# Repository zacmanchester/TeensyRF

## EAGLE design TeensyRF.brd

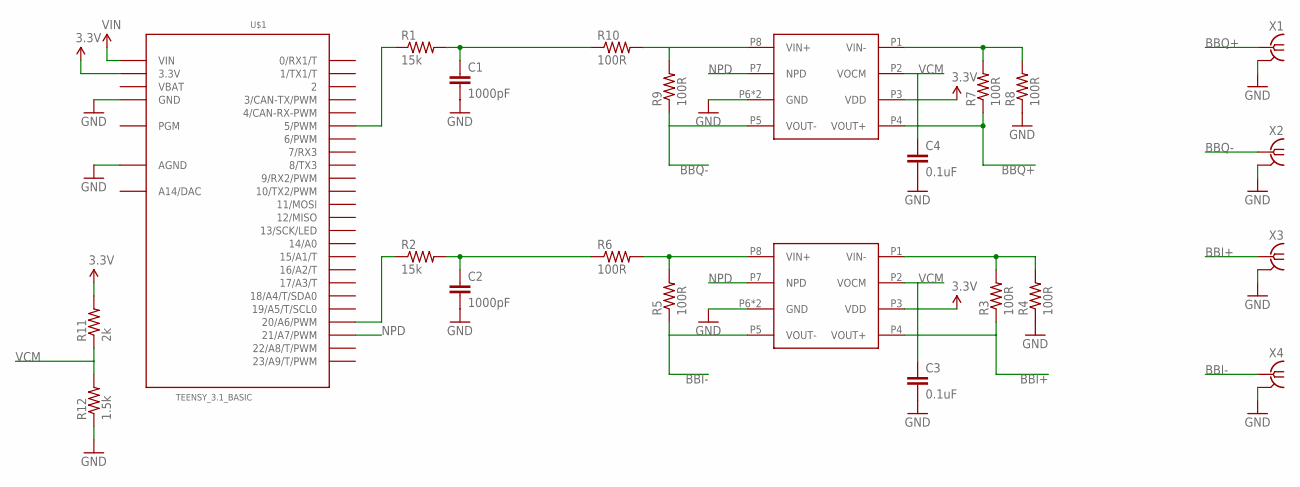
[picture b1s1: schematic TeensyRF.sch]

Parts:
C1, C2: 1000pF; 0805
C3, C4: 0.1uF; 0805
R1, R2: 15k; 0805
R3, R4, R5, R6, R7, R8, R9, R10: 100R; 0805
R11: 2k; 0805
R12: 1.5k; 0805
U$1: TEENSY_3.1_BASIC
U$2, U$3: THS4120; POWERPAD-MSOP-8
X1, X2, X3, X4: SMA-142-0701-801/806; J502-ND-142-0701-801/806

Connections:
3.3V: R11.2, U$1.3.3V, U$1.3.3V1 (3.3V), U$2.P3 (VDD), U$3.P3 (VDD)
BBI+: R3.1, U$3.P4 (VOUT+), X3.1
BBI-: R5.1, U$3.P5 (VOUT-), X4.1
BBQ+: R7.1, U$2.P4 (VOUT+), X1.1
BBQ-: R9.1, U$2.P5 (VOUT-), X2.1
GND: C1.2, C2.2, C3.2, C4.2, R4.1, R8.1, R12.1, U$1.AGND, U$1.GND, U$1.GND1 (GND), U$2.P6 (GND), U$2.PAD (GND), U$3.P6 (GND), U$3.PAD (GND), X1.G@1 (2), X1.G@2 (2), X1.G@3 (2), X1.G@4 (2), X2.G@1 (2), X2.G@2 (2), X2.G@3 (2), X2.G@4 (2), X3.G@1 (2), X3.G@2 (2), X3.G@3 (2), X3.G@4 (2), X4.G@1 (2), X4.G@2 (2), X4.G@3 (2), X4.G@4 (2)
unnamed: R1.1, U$1.5 (5/PWM)
unnamed: C1.1, R1.2, R10.1
unnamed: R2.1, U$1.20/A6 (20/A6/PWM)
unnamed: C2.1, R2.2, R6.1
unnamed: R5.2, R6.2, U$3.P8 (VIN+)
unnamed: R3.2, R4.2, U$3.P1 (VIN-)
unnamed: R7.2, R8.2, U$2.P1 (VIN-)
unnamed: R9.2, R10.2, U$2.P8 (VIN+)
NPD: U$1.21/A7 (21/A7/PWM), U$2.P7 (NPD), U$3.P7 (NPD)
VBAT: U$1.VBAT
VCM: C3.1, C4.1, R11.1, R12.2, U$2.P2 (VOCM), U$3.P2 (VOCM)
VIN: U$1.VIN

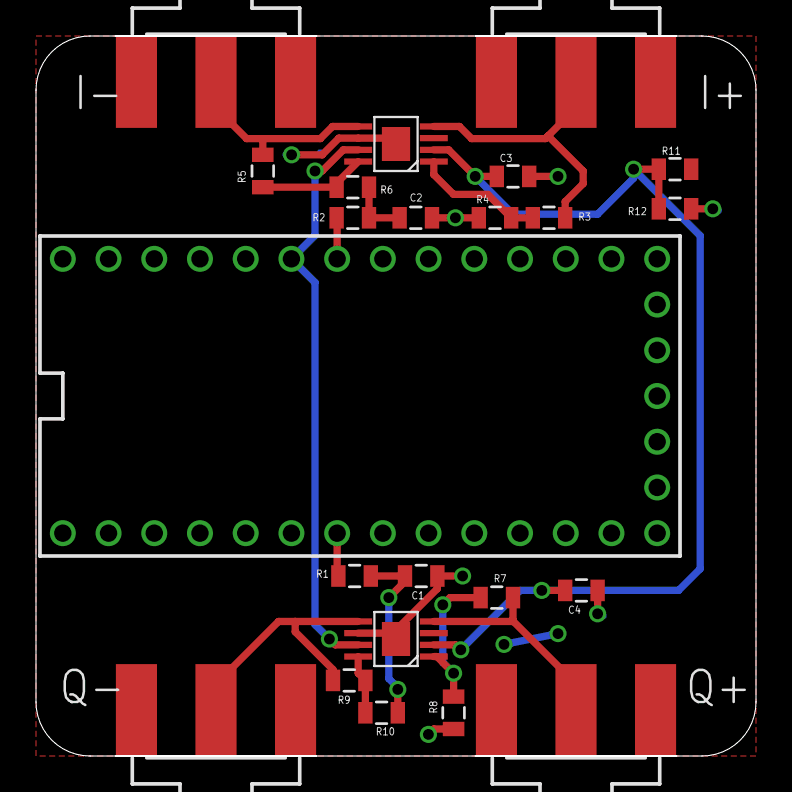
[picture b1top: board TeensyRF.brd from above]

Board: 2 copper layers, 40.0 x 40.0 mm, 23 parts (0 on the bottom side), 16 nets.

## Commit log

2015-06-27 Added library part for THS4120 Diff. Op-Amp
2015-06-28 Beginning of TX side of radio
2015-06-28 Finished TX schematic
2015-06-29 Finished TX Test board layout
2015-06-29 Added silkscreen
2015-07-14 Fixed R11 R12 mixup

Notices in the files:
parts and their libraries:
SparkFun-Capacitors: Licensing: Creative Commons ShareAlike 4.0 International - https://creativecommons.org/licenses/by-sa/4.0
